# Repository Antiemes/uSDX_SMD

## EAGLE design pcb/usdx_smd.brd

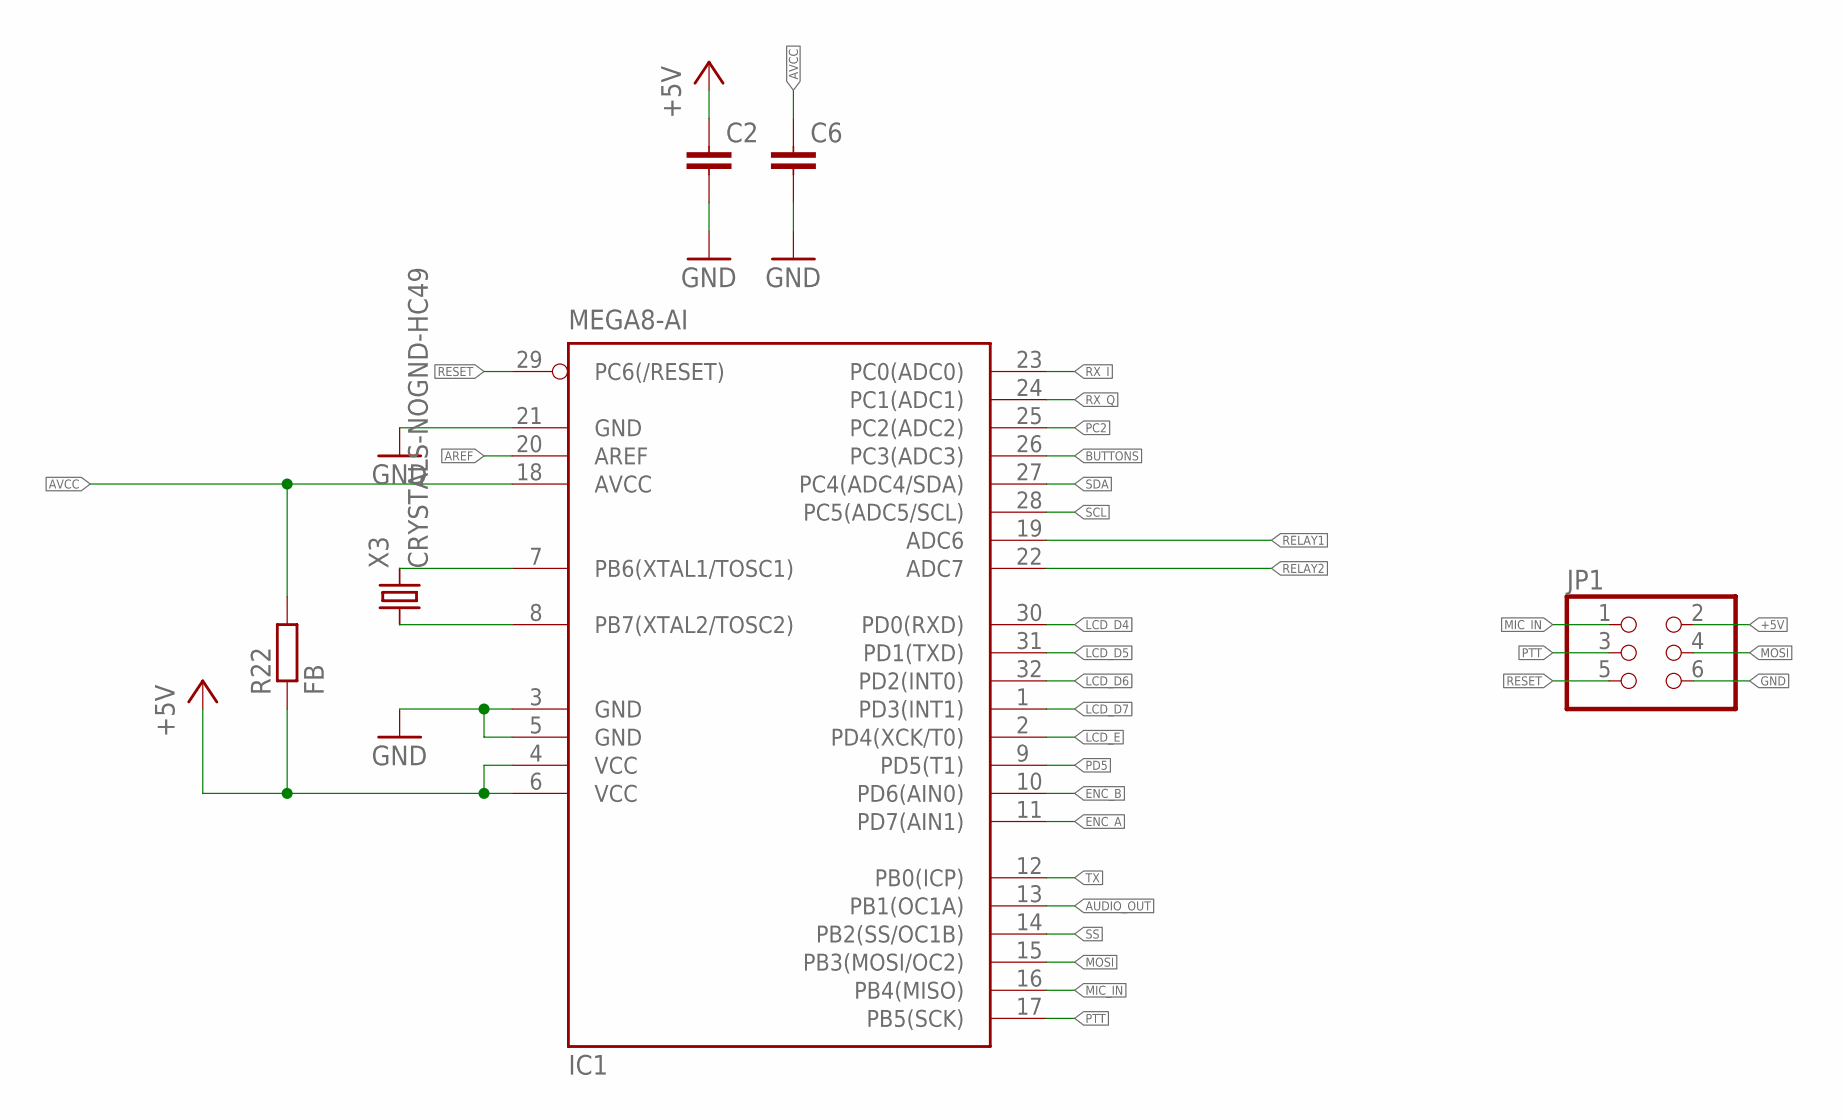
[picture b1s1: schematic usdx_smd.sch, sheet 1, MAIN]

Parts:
C2, C6: C-EUC0603K; C0603K
IC1: MEGA8-AI; TQFP32-08
JP1: PINHD-2X3; 2X03
R22: FB; R1206
X3: CRYSTALS-NOGND-HC49; HC49

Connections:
+5V: C2.1, IC1.4 (VCC), IC1.6 (VCC), JP1.2, R22.1; also elsewhere on the board
AREF: IC1.20 (AREF); also elsewhere on the board
AUDIO_OUT: IC1.13 (PB1(OC1A)); also elsewhere on the board
AVCC: C6.1, IC1.18 (AVCC), R22.2
BUTTONS: IC1.26 (PC3(ADC3)); also elsewhere on the board
ENC_A: IC1.11 (PD7(AIN1)); also elsewhere on the board
ENC_B: IC1.10 (PD6(AIN0)); also elsewhere on the board
GND: C2.2, C6.2, IC1.3 (GND), IC1.5 (GND), IC1.21 (GND), JP1.6; also elsewhere on the board
LCD_D4: IC1.30 (PD0(RXD)); also elsewhere on the board
LCD_D5: IC1.31 (PD1(TXD)); also elsewhere on the board
LCD_D6: IC1.32 (PD2(INT0)); also elsewhere on the board
LCD_D7: IC1.1 (PD3(INT1)); also elsewhere on the board
LCD_E: IC1.2 (PD4(XCK/T0)); also elsewhere on the board
MIC_IN: IC1.16 (PB4(MISO)), JP1.1; also elsewhere on the board
MOSI: IC1.15 (PB3(MOSI/OC2)), JP1.4
unnamed: IC1.7 (PB6(XTAL1/TOSC1)), X3.2
unnamed: IC1.8 (PB7(XTAL2/TOSC2)), X3.1
PC2: IC1.25 (PC2(ADC2))
PD5: IC1.9 (PD5(T1))
PTT: IC1.17 (PB5(SCK)), JP1.3; also elsewhere on the board
RELAY1: IC1.19 (ADC6); also elsewhere on the board
RELAY2: IC1.22 (ADC7); also elsewhere on the board
RESET: IC1.29 (PC6(/RESET)), JP1.5
RX_I: IC1.23 (PC0(ADC0)); also elsewhere on the board
RX_Q: IC1.24 (PC1(ADC1)); also elsewhere on the board
SCL: IC1.28 (PC5(ADC5/SCL)); also elsewhere on the board
SDA: IC1.27 (PC4(ADC4/SDA)); also elsewhere on the board
SS: IC1.14 (PB2(SS/OC1B))
TX: IC1.12 (PB0(ICP)); also elsewhere on the board

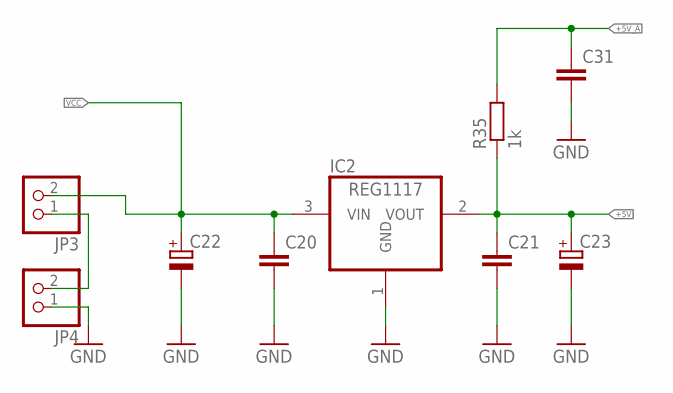
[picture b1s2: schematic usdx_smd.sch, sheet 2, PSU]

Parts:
C20, C21, C31: C-EUC0603K; C0603K
C22: CPOL-EUE5-13; E5-13
C23: CPOL-EUCT7343; CT7343
IC2: REG1117; SOT223
JP3, JP4: PINHD-1X2; 1X02
R35: 1k; M1206

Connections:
+5V: C21.1, C23.+, IC2.2 (VOUT), R35.1; also elsewhere on the board
+5V_A: C31.1, R35.2; also elsewhere on the board
GND: C20.2, C21.2, C22.-, C23.-, C31.2, IC2.1 (GND), JP4.1; also elsewhere on the board
unnamed: JP3.1, JP4.2
VCC: C20.1, C22.+, IC2.3 (VIN), JP3.2; also elsewhere on the board

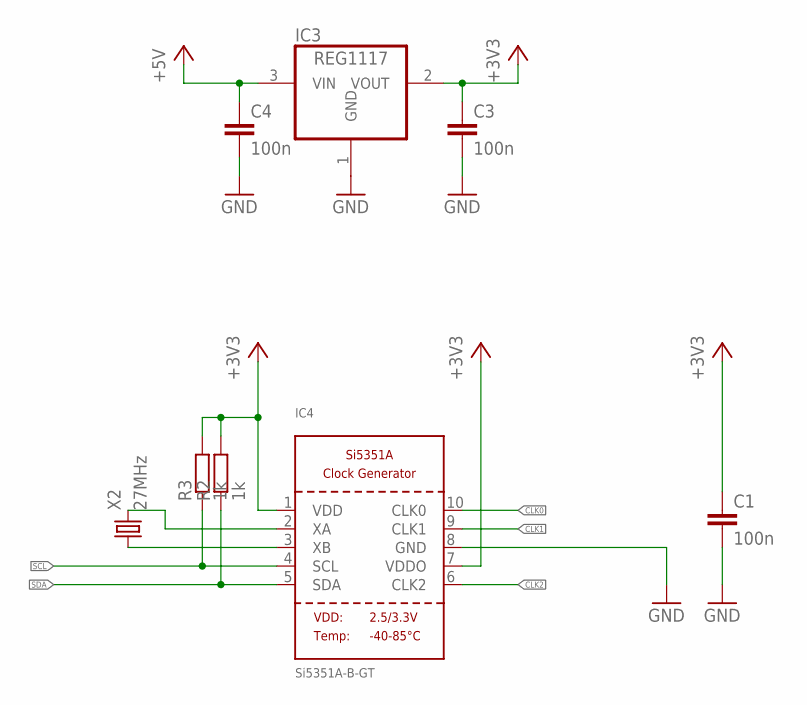
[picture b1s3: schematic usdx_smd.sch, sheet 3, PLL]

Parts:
C1, C3, C4: 100n; C0603K
IC3: REG1117; SOT223
IC4: Si5351A-B-GT; MSOP10
R2, R3: 1k; M1206
X2: 27MHz; HC49

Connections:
+3V3: C1.1, C3.1, IC3.2 (VOUT), IC4.1 (VDD), IC4.7 (VDDO), R2.2, R3.2
+5V: C4.1, IC3.3 (VIN); also elsewhere on the board
CLK0: IC4.10 (CLK0); also elsewhere on the board
CLK1: IC4.9 (CLK1); also elsewhere on the board
CLK2: IC4.6 (CLK2); also elsewhere on the board
GND: C1.2, C3.2, C4.2, IC3.1 (GND), IC4.8 (GND); also elsewhere on the board
unnamed: IC4.3 (XB), X2.1
unnamed: IC4.2 (XA), X2.2
SCL: IC4.4 (SCL), R3.1; also elsewhere on the board
SDA: IC4.5 (SDA), R2.1; also elsewhere on the board

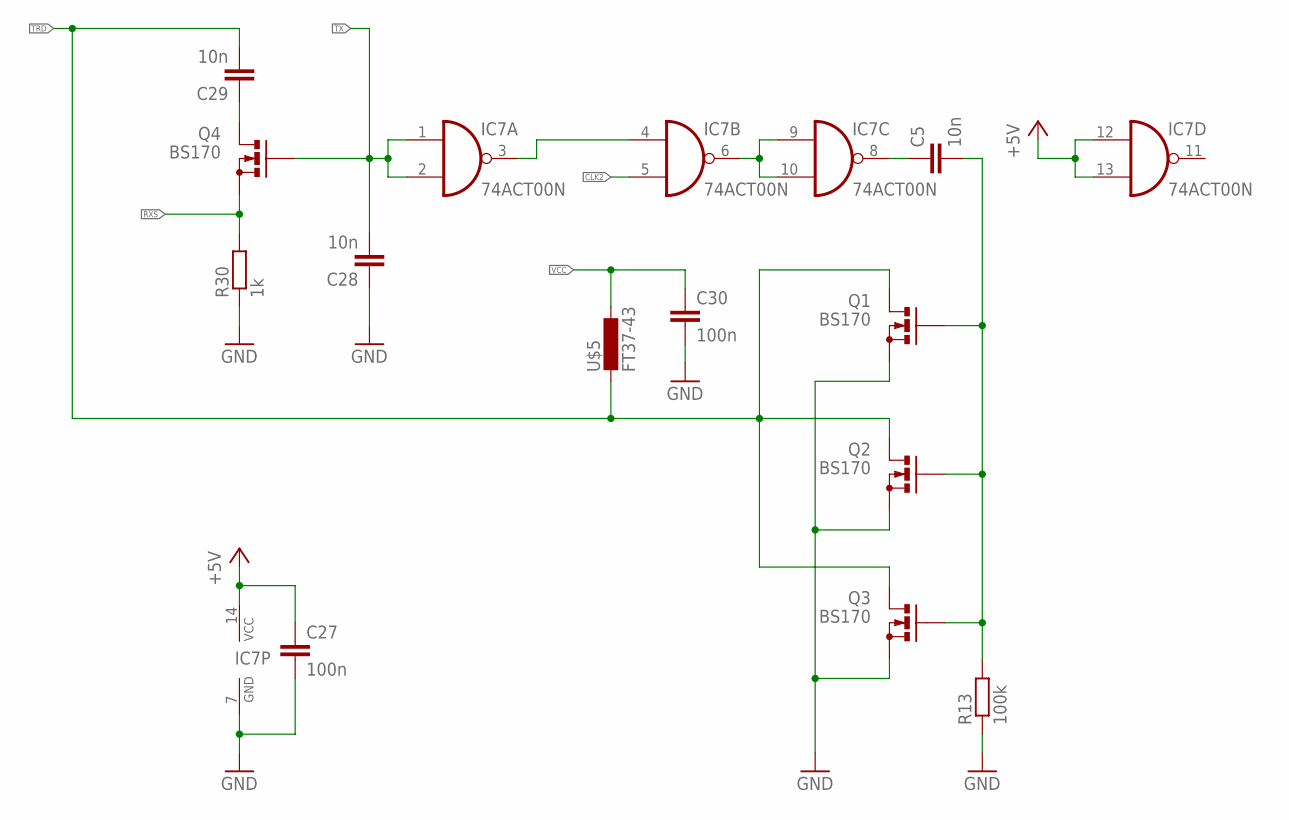
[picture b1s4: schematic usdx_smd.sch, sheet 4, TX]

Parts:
C5: 10n; C0603K
C27, C30: 100n; C0603K
C28, C29: 10n; C1206K
IC7: 74ACT00N; DIL14
Q1, Q2, Q3, Q4: BS170; SOT54E
R13: 100k; M1206
R30: 1k; R1206
U$5: FT37-43; T37

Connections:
+5V: C27.1, IC7.12 (I0), IC7.13 (I1), IC7.14 (VCC); also elsewhere on the board
CLK2: IC7.5 (I1); also elsewhere on the board
GND: C27.2, C28.1, C30.2, IC7.7 (GND), Q1.S, Q2.S, Q3.S, R13.1, R30.1; also elsewhere on the board
unnamed: C5.2, Q1.G, Q2.G, Q3.G, R13.2
unnamed: C29.1, Q4.D
unnamed: IC7.3 (O), IC7.4 (I0)
unnamed: IC7.6 (O), IC7.9 (I0), IC7.10 (I1)
unnamed: C5.1, IC7.8 (O)
RXS: Q4.S, R30.2; also elsewhere on the board
TRD: C29.2, Q1.D, Q2.D, Q3.D, U$5.P$1 (1)
TX: C28.2, IC7.1 (I0), IC7.2 (I1), Q4.G; also elsewhere on the board
VCC: C30.1, U$5.P$2 (2); also elsewhere on the board

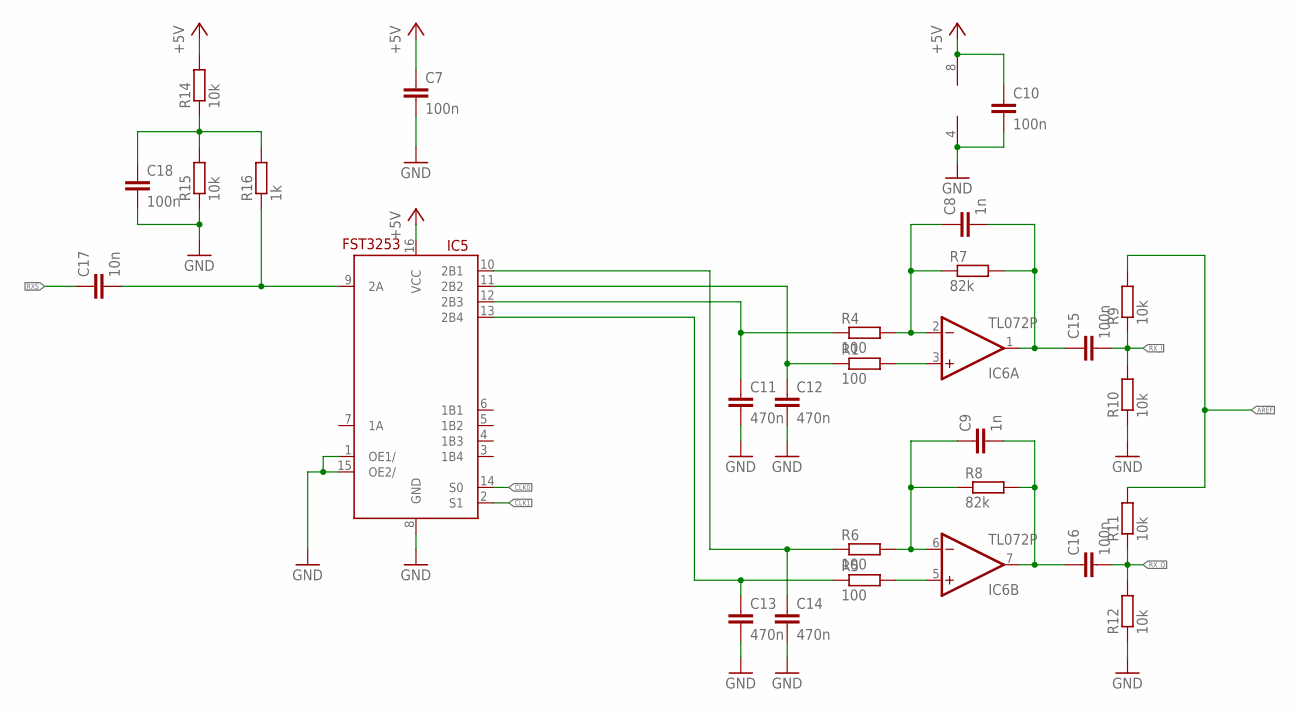
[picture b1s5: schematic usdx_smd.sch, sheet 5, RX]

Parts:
C7, C10, C15, C16, C18: 100n; C0603K
C8, C9: 1n; C0603K
C11, C12, C13, C14: 470n; C1206K
C17: 10n; C1206K
IC5: FST3253; TSSOP16
IC6: TL072P; DIL08
R1, R4, R5, R6: 100; M1206
R7, R8: 82k; M1206
R9, R10, R11, R12, R14, R15: 10k; M1206
R16: 1k; M1206

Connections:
+5V: C7.1, C10.1, IC5.16 (VCC), IC6.8 (V+), R14.2; also elsewhere on the board
AREF: R9.2, R11.2; also elsewhere on the board
CLK0: IC5.14 (S0); also elsewhere on the board
CLK1: IC5.2 (S1); also elsewhere on the board
GND: C7.2, C10.2, C11.2, C12.2, C13.2, C14.2, C18.2, IC5.1 (OE1/), IC5.8 (GND), IC5.15 (OE2/), IC6.4 (V-), R10.1, R12.1, R15.1; also elsewhere on the board
unnamed: IC6.3 (+IN), R1.2
unnamed: C8.1, IC6.2 (-IN), R4.2, R7.1
unnamed: IC6.5 (+IN), R5.2
unnamed: C9.1, IC6.6 (-IN), R6.2, R8.1
unnamed: C11.1, IC5.12 (2B3), R4.1
unnamed: C12.1, IC5.11 (2B2), R1.1
unnamed: C8.2, C15.1, IC6.1 (OUT), R7.2
unnamed: C13.1, IC5.13 (2B4), R5.1
unnamed: C9.2, C16.1, IC6.7 (OUT), R8.2
unnamed: C14.1, IC5.10 (2B1), R6.1
unnamed: C18.1, R14.1, R15.2, R16.2
unnamed: C17.2, IC5.9 (2A), R16.1
RXS: C17.1; also elsewhere on the board
RX_I: C15.2, R9.1, R10.2; also elsewhere on the board
RX_Q: C16.2, R11.1, R12.2; also elsewhere on the board

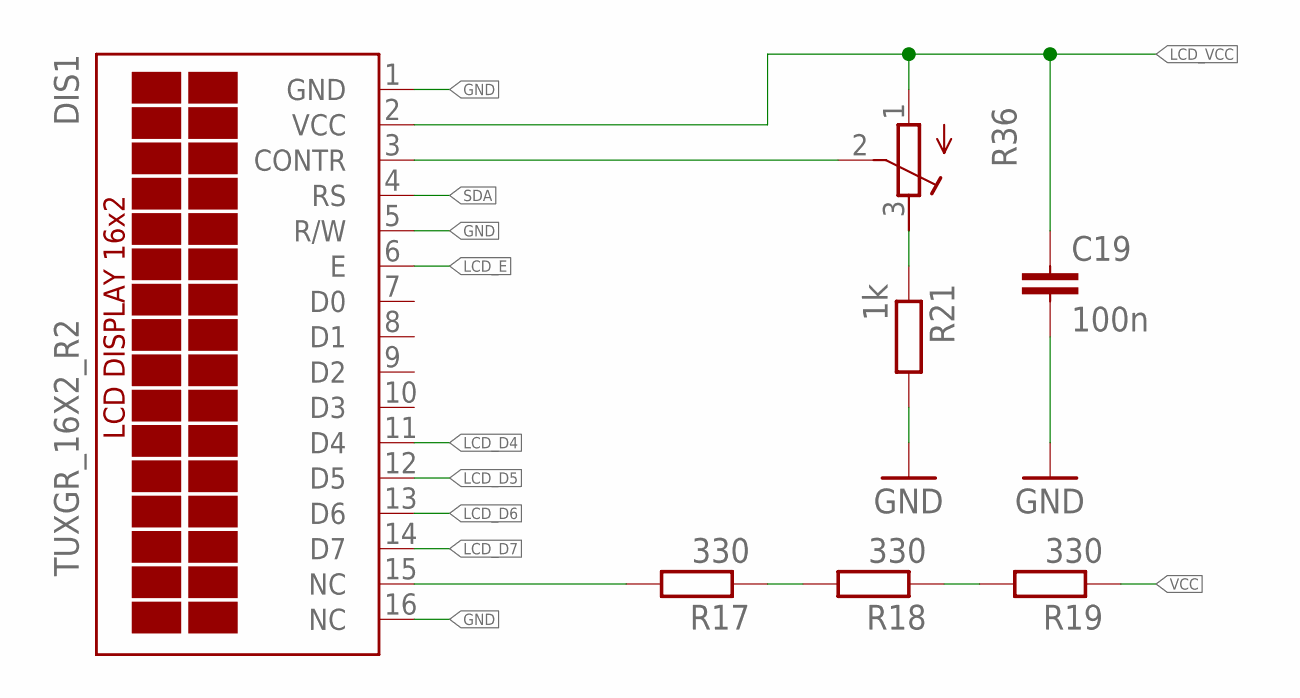
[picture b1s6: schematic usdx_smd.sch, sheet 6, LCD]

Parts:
C19: 100n; C0603K
DIS1: TUXGR_16X2_R2
R17, R18, R19: 330; M1206
R21: 1k; M1206
R36: R-TRIMM3374; RTRIM3374

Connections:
GND: C19.2, DIS1.1 (GND), DIS1.5 (R/W), DIS1.16 (NC), R21.2; also elsewhere on the board
LCD_CONTR: DIS1.3 (CONTR), R36.2 (S)
LCD_D4: DIS1.11 (D4); also elsewhere on the board
LCD_D5: DIS1.12 (D5); also elsewhere on the board
LCD_D6: DIS1.13 (D6); also elsewhere on the board
LCD_D7: DIS1.14 (D7); also elsewhere on the board
LCD_E: DIS1.6 (E); also elsewhere on the board
LCD_VCC: C19.1, DIS1.2 (VCC), R36.1 (A)
unnamed: R17.1, R18.2
unnamed: DIS1.15 (NC), R17.2
unnamed: R18.1, R19.2
unnamed: R21.1, R36.3 (E)
SDA: DIS1.4 (RS); also elsewhere on the board
VCC: R19.1; also elsewhere on the board

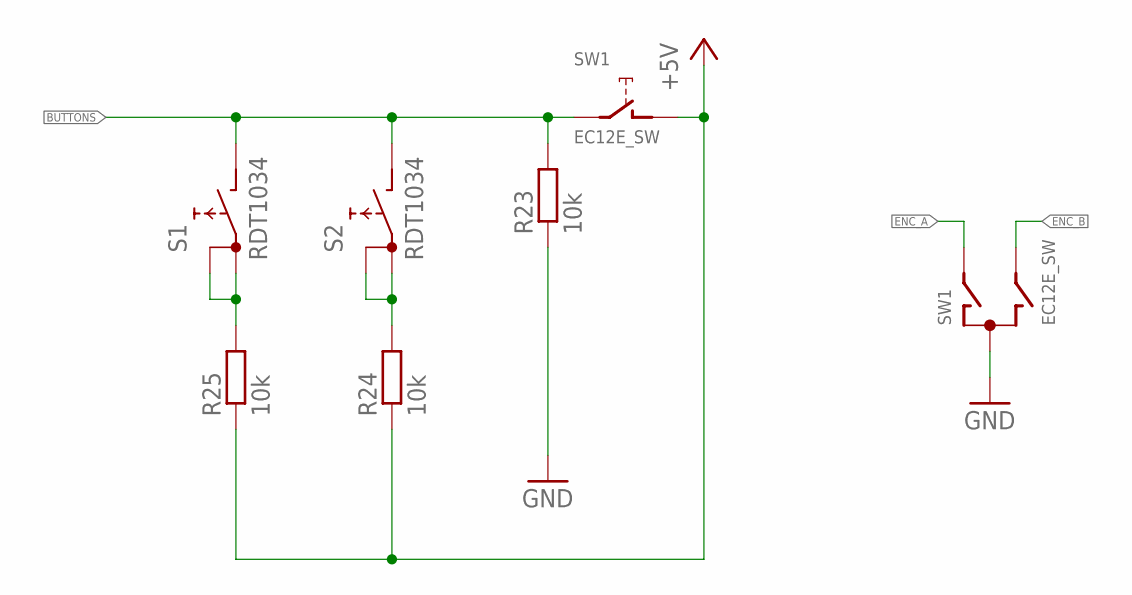
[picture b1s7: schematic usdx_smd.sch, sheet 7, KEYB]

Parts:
R23, R24, R25: 10k; M1206
S1, S2: RDT1034
SW1: EC12E_SW; ALPS_EC12E_SW

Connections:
+5V: R24.1, R25.1, SW1.D (1); also elsewhere on the board
BUTTONS: R23.2, S1.B, S2.B, SW1.E (2); also elsewhere on the board
ENC_A: SW1.A; also elsewhere on the board
ENC_B: SW1.B; also elsewhere on the board
GND: R23.1, SW1.C; also elsewhere on the board
unnamed: R24.2, S2.A, S2.A1
unnamed: R25.2, S1.A, S1.A1

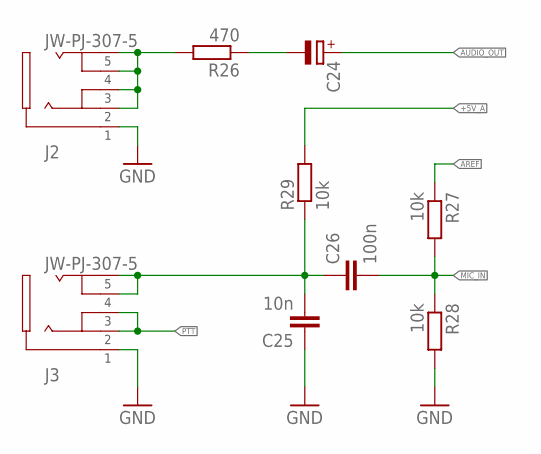
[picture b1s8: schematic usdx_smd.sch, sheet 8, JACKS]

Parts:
C24: CPOL-EUCT7343; CT7343
C25: 10n; C1206K
C26: 100n; C0603K
J2, J3: JW-PJ-307-5; JW-PJ-307-X
R26: 470; M1206
R27, R28, R29: 10k; M1206

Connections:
+5V_A: R29.2; also elsewhere on the board
AREF: R27.1; also elsewhere on the board
AUDIO_OUT: C24.+; also elsewhere on the board
GND: C25.1, J2.P$1 (1), J3.P$1 (1), R28.2; also elsewhere on the board
MIC_IN: C26.2, R27.2, R28.1; also elsewhere on the board
unnamed: C24.-, R26.1
unnamed: C25.2, C26.1, J3.P$4 (4), J3.P$5 (5), R29.1
unnamed: J2.P$2 (2), J2.P$3 (3), J2.P$4 (4), J2.P$5 (5), R26.2
PTT: J3.P$2 (2), J3.P$3 (3); also elsewhere on the board

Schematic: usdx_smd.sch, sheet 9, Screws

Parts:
H1, H2, H3, H4: MOUNT-PAD-ROUND3.2; 3,2-PAD

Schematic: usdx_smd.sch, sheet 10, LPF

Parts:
CF1-A, CF1-B, CF2-A, CF2-B, CF3-A, CF3-B, CF4-A, CF4-B, CF5-A, CF5-B, CF6-A, CF6-B: C-EU025-024X044; C025-024X044
K1, K2: TQ2SA-L2-5V; TQ-SA
L1-A, L1-B, L2-A, L2-B: T37
R31, R32, R33, R34: 1k; R1206
T1, T2: -NPN-SOT23-EBC; SOT23-EBC
X1: BU-SMA-H

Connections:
+5V: K1.1 (+), K1.10 (+), K2.1 (+), K2.10 (+); also elsewhere on the board
GND: CF1-A.2, CF1-B.2, CF4-A.1, CF4-B.1, CF6-A.2, CF6-B.2, K1.8, K2.3, R33.2, R34.2, T1.E, T2.E, X1.2, X1.3 (2), X1.4 (2), X1.5 (2); also elsewhere on the board
unnamed: K1.6 (-), K2.6 (-), T1.C
unnamed: K1.5 (-), K2.5 (-), T2.C
unnamed: R31.1, T1.B
unnamed: R32.1, T2.B
unnamed: K1.3, X1.1
unnamed: CF5-A.1, CF6-A.1, K1.4 (S), K1.9 (O), L2-A.P$1 (1)
unnamed: CF2-A.2, CF3-A.2, CF4-A.2, CF5-A.2, L2-A.P$2 (2)
unnamed: CF5-B.1, CF6-B.1, K1.2 (O), K1.7 (S), L2-B.P$1 (1)
unnamed: CF2-B.2, CF3-B.2, CF4-B.2, CF5-B.2, L2-B.P$2 (2)
unnamed: CF2-B.1, CF3-B.1, L1-B.P$1 (1)
unnamed: CF2-A.1, CF3-A.1, L1-A.P$1 (1)
unnamed: CF1-A.1, K2.2 (O), K2.7 (S), L1-A.P$2 (2)
unnamed: CF1-B.1, K2.4 (S), K2.9 (O), L1-B.P$2 (2)
RELAY1: R31.2, R34.1; also elsewhere on the board
RELAY2: R32.2, R33.1; also elsewhere on the board

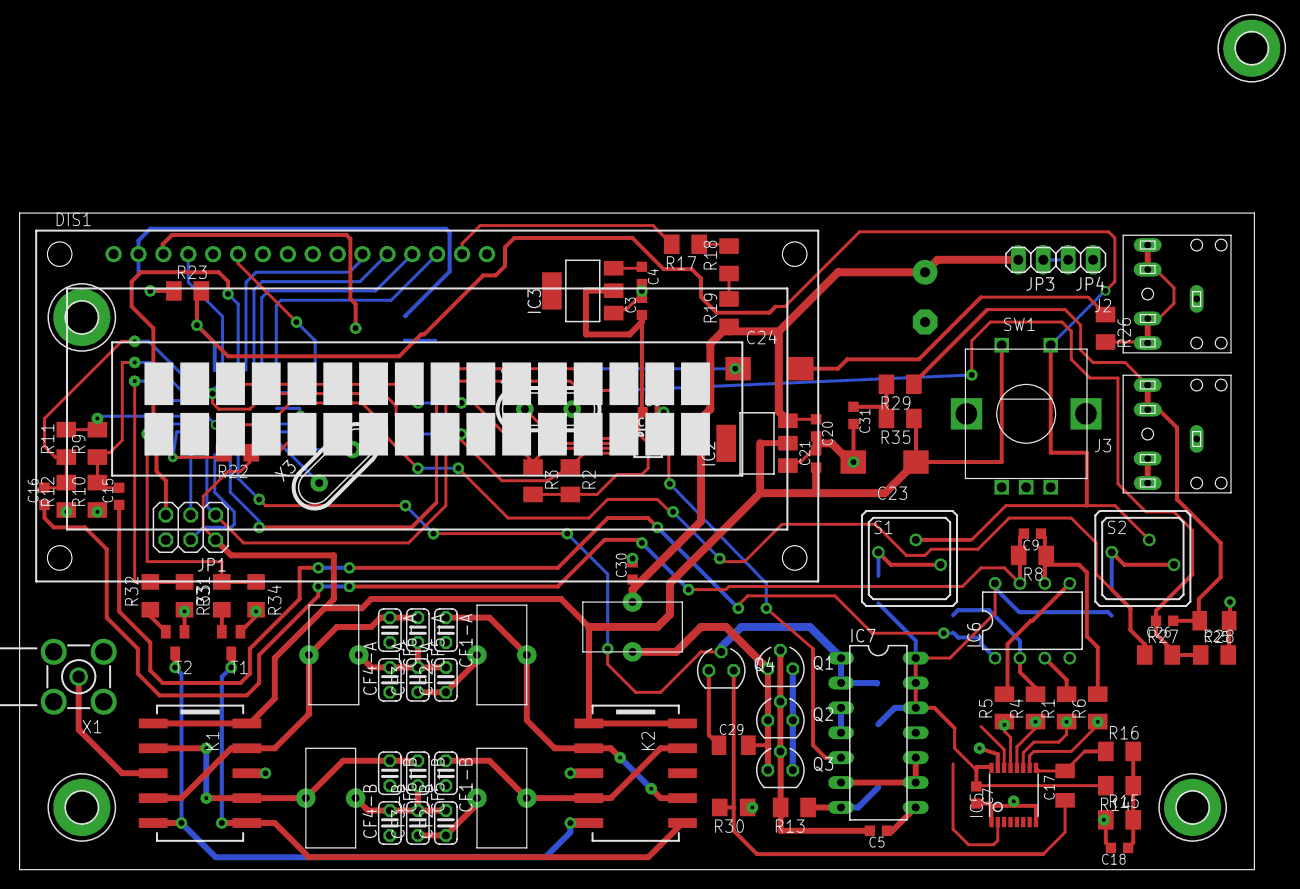
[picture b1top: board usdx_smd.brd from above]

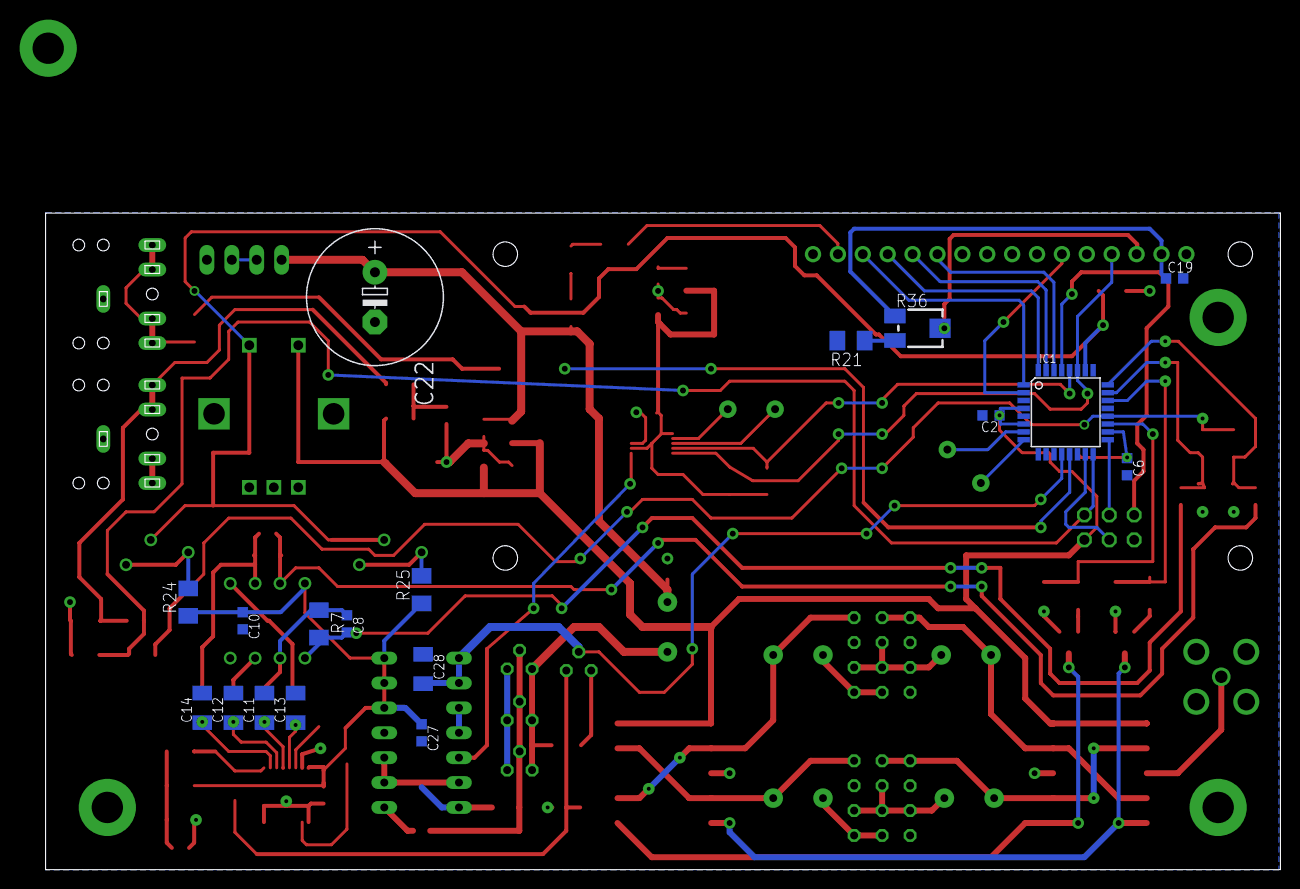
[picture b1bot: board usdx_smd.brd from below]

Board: 2 copper layers, 126.0 x 67.0 mm, 114 parts (18 on the bottom side), 78 nets.

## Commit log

2021-03-04 Schematics on 80%
2021-03-06 Schematics maybe complete.
2021-03-09 Schematics 99%, placing started.
2021-03-09 More routing
2021-12-09 Much much routing
2021-12-25 Some more routing
2021-12-26 And more routing
2022-07-15 Two invisible unrouted signals routed

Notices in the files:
parts and their libraries:
microbuilder: This work is placed in the public domain, and may be freely used for commercial and non-commercial work with the following conditions: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
